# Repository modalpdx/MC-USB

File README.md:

#MC-USB Development Board

*BIGGER, MORE IMPORTANT NOTE: This project is being abandoned. I could fix
the issues with the board, but since getting the first run back from the
fab I have discovered the [Little Wire](http://littlewire.cc "Little Wire") 
project, which more or less encompasses everything I set out to do
with MC-USB. Please forget MC-USB exists and check out Little Wire
instead. You won't regret it.*

*BIG IMPORTANT NOTE: The first run of PCBs has come back from the fab, and
yep, they don't work as designed. Until further notice, please don't make
any PCBs from these files. I'll update everything once I figure out how to
fix all of the issues. There aren't many, but the ones that exist are show
stoppers as far as I'm concerned.*

A board that should have all the hardware that you need to experiment with
V-USB or any other software-based USB stack on an ATTINY-85 MCU (current
configuration, other MCUs may be implemented in future editions). 

The design of this board originated with the AVR/V-USB schematics found in
Code and Life's AVR ATTINY USB Tutorial (linked below). I combined their schematics for
ATTINY-2313 and ATTINY-85 circuits and added an ISP header. 

*Note: the ISP header does not utilize VCC or GND. All power to this board
comes from the USB connection. Please keep this in mind if you decide to
program the MCU on this board.*

The ISP header doubles as a pinout for the ATTINY-85 chip. The "useful"
pins are labeled along with their ISP usages (MISO, MOSI, etc).

There is a spot on the board for a 12MHz external crystal. I would suggest
adding a 3-pin female header here instead, reason being the ATTINY-85's
internal 16.5MHz oscillator can be utilized in place of a crystal, and
that frees up the crystal pins (PB3 and PB4) for other uses. A crystal
will fit in a 3-pin female header just fine if one is used, otherwise the
header will give you much easier access to the freed pins. It's your call.

##Parts

* ATTINY-85 PDIP-8 AVR MCU
* 8 pin DIP socket
* 2-68k ohm 1/4 watt resistors (R1, R2)
* 2.2k ohm 1/4 watt resistor (R4)
* 4.7k ohm 1/4 watt resistor (R3)
* 10uF polarized capacitor (C1)
* 0.1uF ceramic capacitor (C2)
* 2-22pF ceramic capacitors (C3, C4)
* 2-3.6V 1/2 watt Zener diodes (D1, D2)
* 2x6 male header pins (ISP)
* 12MHz external crystal (optional)
* 3-pin female header for crystal (optional)
* Mini-B 5-pin SMT female USB connector (there are many, but they are similar. The version I used has two plastic pins that keep it from sliding horizontally on the board.)

##Resources

I'm not going to document V-USB usage, sorry. There are tutorials linked
to the V-USB page and numerous websites Out There™ that cover this in
detail. 

* [V-USB Website](http://www.obdev.at/products/vusb/index.html "V-USB Website") 
* [Code and Life's AVR ATTINY USB Tutorial](http://codeandlife.com/2012/01/22/avr-attiny-usb-tutorial-part-1/ "Code and Life's V-USB ATTINY Tutorial")

##Limitations

* I'm not 100% sure I got the ISP implemented correctly. Buyer beware.
* I'm not 100% sure I got the crystal set up correctly to allow PB3 and PB4 pin access if no crystal is used. Buyer beware again.

##Motivation

After successfully working up a breadboard with an ATTINY-85/V-USB
circuit, I realized there was no way in hell I was going through that
every time I wanted to work with AVR/USB stacks. A board that could take a
fresh (or flashed) ATTINY-85 would exponentially speed up the development
process. So, here we are.

##Miscellaneous Notes

Don't use these files yet. Moose out front should have told you.

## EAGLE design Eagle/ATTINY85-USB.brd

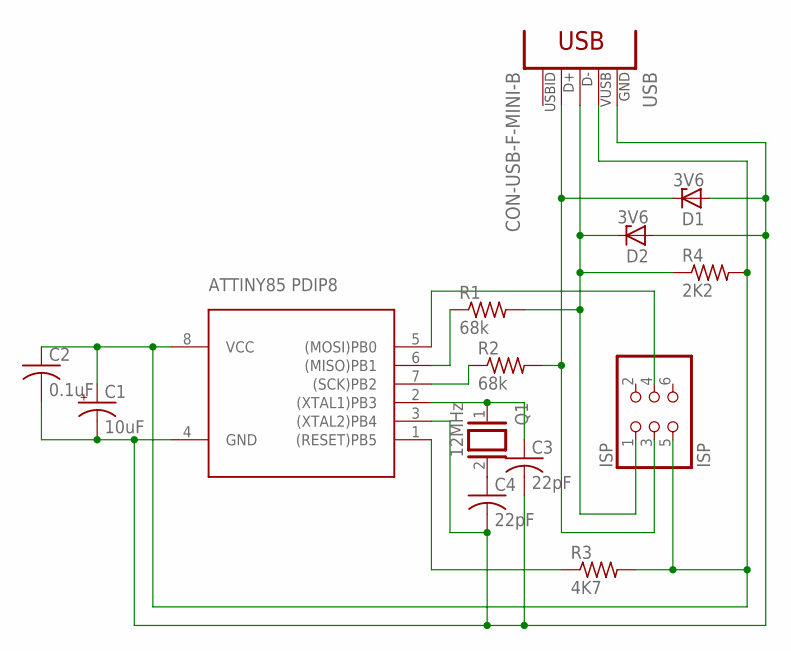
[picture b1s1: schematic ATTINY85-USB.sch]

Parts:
C1: 10uF; E2-4
C2: 0.1uF; C025-024X044
C3, C4: 22pF; C025-024X044
D1, D2: 3V6; DO34Z7
IC1: TINY85; DIL08
ISP: ISP; 2X03
Q1: 12MHz; QS
R1, R2: 68k; 0207/9
R3: 4K7; 0207/9
R4: 2K2; 0207/9
USB: CON-USB-F-MINI-B; CONN_USB_MINI-B

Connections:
unnamed: IC1.6 ((MISO)PB1), R1.1
unnamed: D2.C, ISP.1, R1.2, R4.1, USB.D-
unnamed: D1.C, ISP.3, R2.2, USB.D+
unnamed: IC1.5 ((MOSI)PB0), ISP.4
unnamed: IC1.1 ((RESET)PB5), R3.1
unnamed: C4.1, Q1.2
unnamed: C3.1, IC1.2 ((XTAL1)PB3), Q1.1
unnamed: C1.+, C2.1, IC1.8 (VCC), ISP.5, R3.2, R4.2, USB.VUSB
unnamed: IC1.7 ((SCK)PB2), R2.1
unnamed: C1.-, C2.2, C3.2, C4.2, D1.A, D2.A, IC1.3 ((XTAL2)PB4), IC1.4 (GND), USB.GND

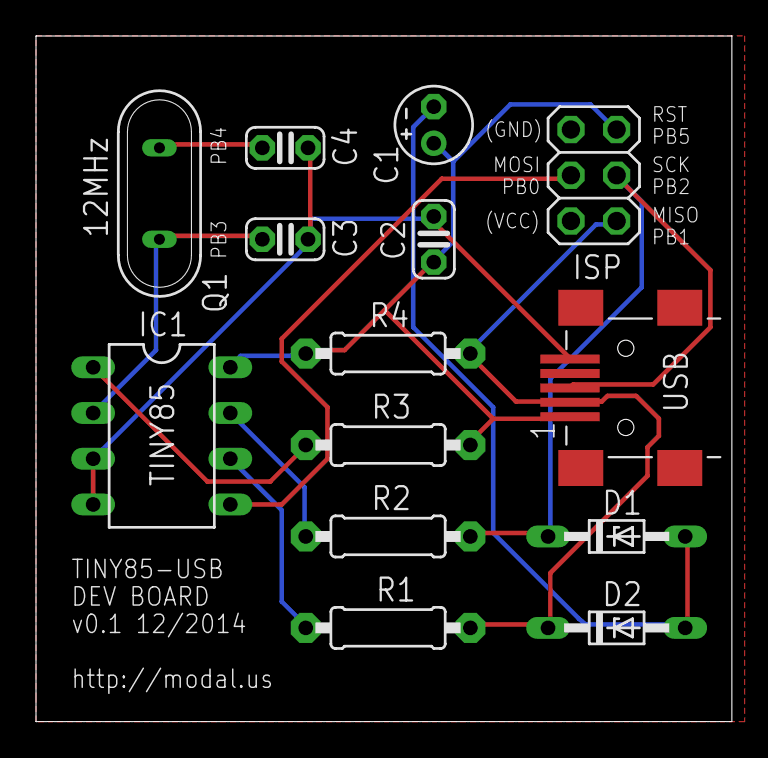
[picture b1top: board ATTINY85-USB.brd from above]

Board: 2 copper layers, 38.7 x 38.1 mm, 14 parts (0 on the bottom side), 10 nets.

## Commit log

2014-12-18 Initial checkin
2014-12-18 Removed pointless mention of V-USB website.
2014-12-18 Updated schematic PDF
2014-12-18 Added a license.
2014-12-18 Bad link syntax.
2014-12-18 More bad link syntax. Markdown is a pain.
2014-12-18 Typos, editing. Stuff.
2015-01-04 Gerbers, updated README (boards don't work yet).
2015-04-03 Expanded title/explanation to include possible non-AVR MCUs.
2015-05-14 Updated README to point to Little Wire.
